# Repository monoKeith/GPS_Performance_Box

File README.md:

# GPS_Performance_Box
Performance box based on ublox-GPS-module and ESP32 S2

## Video

[0 - 100 KPH test](https://youtu.be/5jb0r1BLMyU)

## Pics

---
## Purpose

The purose of this project is to implement a GPS location based speedometer to test acceleration of my car. 

Similar products like [dragy](https://dragymotorsports.com) does not have a display so requires an APP and connection to a phone to work, although it provides more detail it's not very convenient to use.

This project is based on ESP32, so WiFi and Bluetooth connectivity is already onboard just require more software to make it work. And there're redundant IO ports to connect more sensors like an accelerometer, to improve or compensate the results from GPS.

## Functionality

There's 4 different screen.

- Debug screen: shows time, date, speed, location, system uptime
- 0 - 60 timer
- 0 - 80 timer
- 0 - 100 timer

Use yellow button to go to previous screen, use green button to go to next screen. In a timer screen, press red button can reset the results of the displaying timer.

Each of these 3 timers runs in background simultaneously, no need to be in a specific screen.

Automatically test acceleration, all timers are automatically triggered when speed change from 0 - 1, and will automatically stop when the target speed is reached. If target is not reached and speed falls back to 0, the timer resets and wait for speed to change from 0 - 1.

## Issues

- Currently I've noticed that the GPS speed is not reliable at low speed. It constantly jumps between 0 - 1 KPH when it's not moving at all. So instead of testing acceleration of like 0 - 100, it's actually testing 1 - 100. A future update to use accelerometer as timer trigger may mitigate this issue.

- The breakout board design was from my other project, so it wasn't optimized for the space and hardware of this project. All IO connections coulbe be routed in a better way to achieve a much compact design.

- It doesn't have a battery, requires USB power to work.

## Libraries
[SparkFun u-blox GNSS Arduino Library](https://github.com/sparkfun/SparkFun_u-blox_GNSS_Arduino_Library)

[Thingpulse ESP32 OLED driver for SSD1306](https://github.com/ThingPulse/esp8266-oled-ssd1306)

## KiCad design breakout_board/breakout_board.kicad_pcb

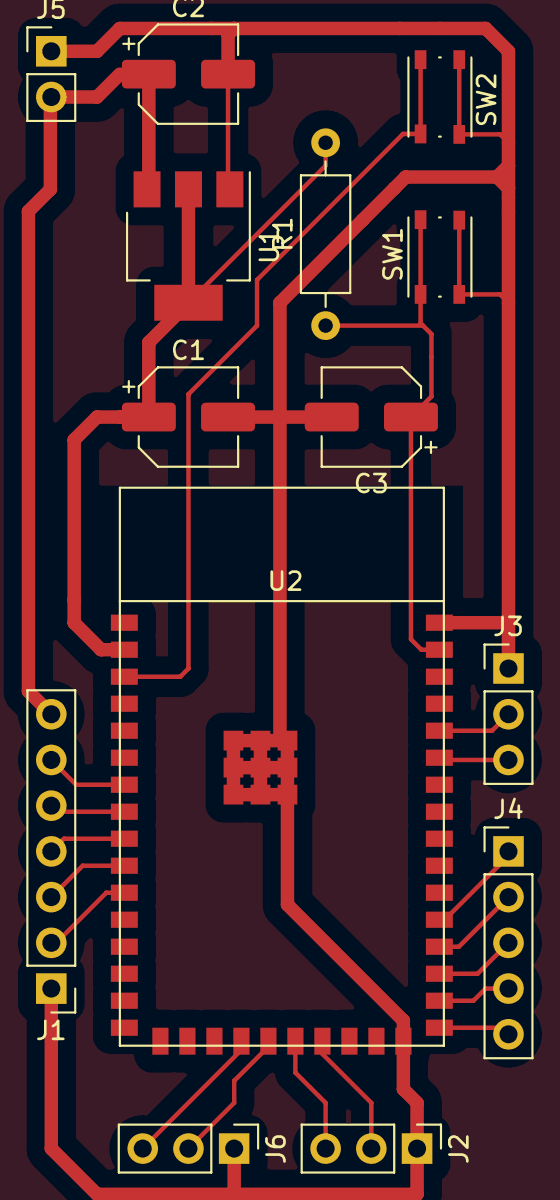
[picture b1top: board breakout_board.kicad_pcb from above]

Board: 2 copper layers, 14 parts (0 on the bottom side), 21 nets.

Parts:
C1: 10uF; CP_Elec_5x5.9
C2: 20uF; CP_Elec_5x5.9
C3: 1uF; CP_Elec_5x5.9
J1: FrontPanel; PinHeader_1x07_P2.54mm_Vertical
J2: USB; PinHeader_1x03_P2.54mm_Vertical
J3: Serial 0; PinHeader_1x03_P2.54mm_Vertical
J4: OUT; PinHeader_1x05_P2.54mm_Vertical
J5: Conn_01x02; PinHeader_1x02_P2.54mm_Vertical
J6: Serial 1; PinHeader_1x03_P2.54mm_Vertical
R1: 10K; R_Axial_DIN0207_L6.3mm_D2.5mm_P10.16mm_Horizontal
SW1: Reset; SW_Push_1P1T_NO_Vertical_Wuerth_434133025816
SW2: Boot; SW_Push_1P1T_NO_Vertical_Wuerth_434133025816
U1: AMS1117-3.3; SOT-223-3_TabPin2
U2: ESP32-S2-WROOM

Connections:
+3V3: C1.1, R1.2, U1.2 (VO), U2.2 (3V3)
+5V: C2.1, J1.7, J5.2, U1.3 (VI)
GND: C1.2, C2.2, C3.2, J1.1, J2.1, J3.1, J5.1, J6.1, SW1.2, SW2.1, U1.1 (GND), U2.26 (GND), U2.42 (GND), U2.43 (EPAD)
unnamed: C3.1, R1.1, SW1.1, U2.41 (EN)
unnamed: J1.2, U2.11 (IO8)
unnamed: J1.3, U2.10 (IO7)
unnamed: J1.4, U2.9 (IO6)
unnamed: J1.5, U2.8 (IO5)
unnamed: J1.6, U2.7 (IO4)
unnamed: J2.2, U2.23 (IO20)
unnamed: J2.3, U2.22 (IO19)
unnamed: J3.2, U2.38 (RXD0)
unnamed: J3.3, U2.37 (TXD0)
unnamed: J4.1, U2.31 (IO37)
unnamed: J4.2, U2.30 (IO36)
unnamed: J4.3, U2.29 (IO35)
unnamed: J4.4, U2.28 (IO34)
unnamed: J4.5, U2.27 (IO33)
unnamed: SW2.2, U2.3 (IO0)
unnamed: J6.3, U2.20 (IO17)
unnamed: J6.2, U2.21 (IO18)

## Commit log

2022-05-07 Included libraries
    ublox-gps & SSD1306 OLED
2022-06-22 Boot screen
2022-08-19 Add PCB design
2022-08-21 [WIP] GPS initialization
2022-08-21 Try baud rates to connect GPS
2022-08-23 Display Time
2022-08-23 Set GPS 10Hz report rate
2022-08-25 Display Location
2022-08-25 Display Speed
2022-08-26 [WIP] Timer
2022-08-27 Timer bug fix
2022-08-30 Button: switch between display modes
2022-09-11 [WIP] 3 Buttons support
2022-09-11 Refactor Timer UI
2022-09-11 Change to 1 decimal place
